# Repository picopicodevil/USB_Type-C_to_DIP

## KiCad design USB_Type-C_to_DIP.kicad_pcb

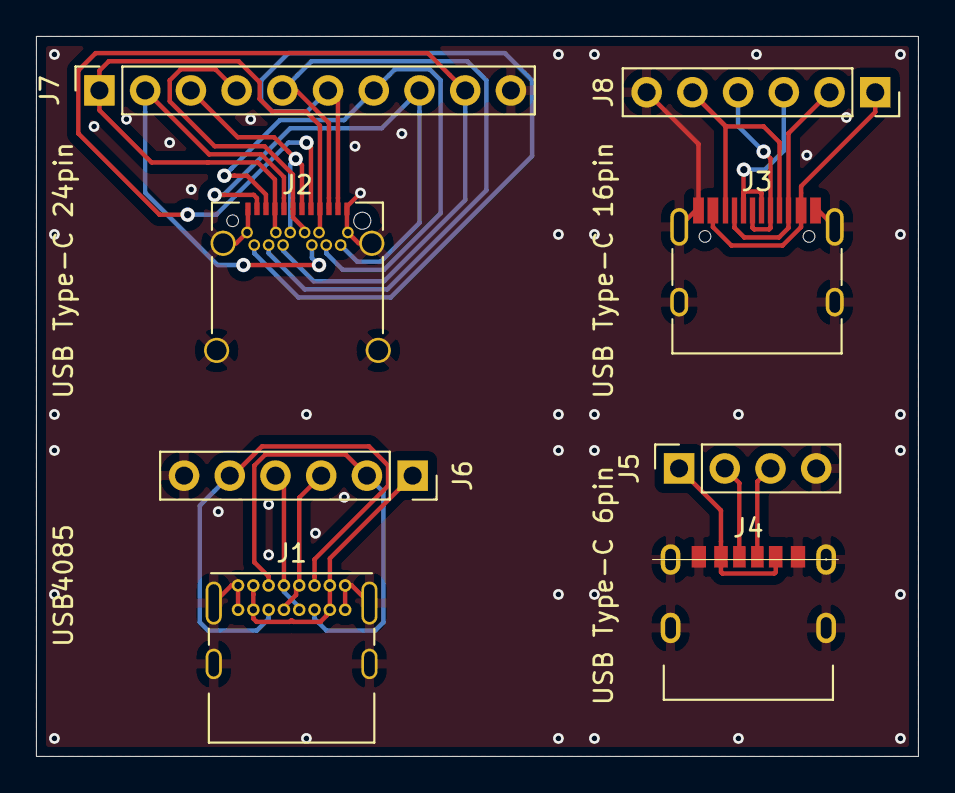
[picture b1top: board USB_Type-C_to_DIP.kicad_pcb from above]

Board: 2 copper layers, 49.0 x 40.0 mm, 8 parts (0 on the bottom side), 23 nets.

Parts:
J1: USB_C_Receptacle; USB_C_Receptacle_GCT_USB4085
J2: USB_C_Receptacle; USB_C_Receptacle_Amphenol_12401548E4-2A_CircularHoles
J3: USB_C_Receptacle; USB_C_Receptacle_HRO_TYPE-C-31-M-12
J4: USB_C_Receptacle_USB2.0; USB_C_Receptacle_6pin
J5: Conn_01x04; PinSocket_1x04_P2.54mm_Vertical
J6, J8: Conn_01x06; PinSocket_1x06_P2.54mm_Vertical
J7: Conn_01x10; PinSocket_1x10_P2.54mm_Vertical

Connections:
GND: J1.A1, J1.A12, J1.B1, J1.B12, J1.S1, J2.A1, J2.A12, J2.B1, J2.B12, J2.S1, J3.A1, J3.A12, J3.B1, J3.B12, J3.S1, J4.A12, J4.B12, J4.S1, J5.4, J6.6, J7.10, J8.6
unnamed: J1.A4, J1.A9, J1.B4, J1.B9, J6.1
unnamed: J1.A5, J1.B5, J6.2
unnamed: J1.A6, J1.B6, J6.4
unnamed: J1.A7, J1.B7, J6.3
unnamed: J1.A8, J1.B8, J6.5
unnamed: J2.A2, J2.B2, J7.8
unnamed: J2.A3, J2.B3, J7.7
unnamed: J2.A4, J2.A9, J2.B4, J2.B9, J7.1
unnamed: J2.A5, J2.B5, J7.2
unnamed: J2.A6, J2.B6, J7.4
unnamed: J2.A7, J2.B7, J7.3
unnamed: J2.A8, J2.B8, J7.9
unnamed: J2.A10, J2.B10, J7.5
unnamed: J2.A11, J2.B11, J7.6
unnamed: J3.A4, J3.A9, J3.B4, J3.B9, J8.1
unnamed: J3.A5, J3.B5, J8.2
unnamed: J3.A6, J3.B6, J8.4
unnamed: J3.A7, J3.B7, J8.3
unnamed: J3.A8, J3.B8, J8.5
unnamed: J4.A9, J4.B9, J5.1
unnamed: J4.A5, J5.2
unnamed: J4.B5, J5.3

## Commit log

2020-03-05 gerber to order
2021-09-26 Create LICENSE
